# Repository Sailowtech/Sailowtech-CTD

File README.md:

# Sailowtech-CTD - Low-Tech CTD Probe
Welcome on the repository of the Sailowtech CTD Project, an affordable and open-source CTD probe tailored for scientific expeditions.

## Why does this project exist?
After all, Open Source CTD probes already exist? Indeed, there are some great projects like [Open CTD](https://github.com/OceanographyforEveryone/OpenCTD "Open CTD Project") or [CTDizzle](https://github.com/IanTBlack/CTDizzle/tree/main "CTDizzle Project"), but we wanted something more tailored for mid to long term expeditions while allowing a modularity in the embedded sensors. Therefore, we aim to develop a project around a main electronic core and auxiliary cards that can be swapped depending on the research interest. For the moment, we propose a core based on a Raspberry PI Zero 2 W and an auxiliary cards for 2 Atlas Scientific Sensors (Conductivity, Temperature, Dissolved Oxygen, pH...).

## Issues
If you encounter any issues, please use the Issue tracker on GitHub. Please note that this project is still in the development phase and currently undergoing testing.

## Full documentation
The full documentation is accessible under [https://sailowtech.github.io/Sailowtech-CTD/](https://sailowtech.github.io/Sailowtech-CTD/)

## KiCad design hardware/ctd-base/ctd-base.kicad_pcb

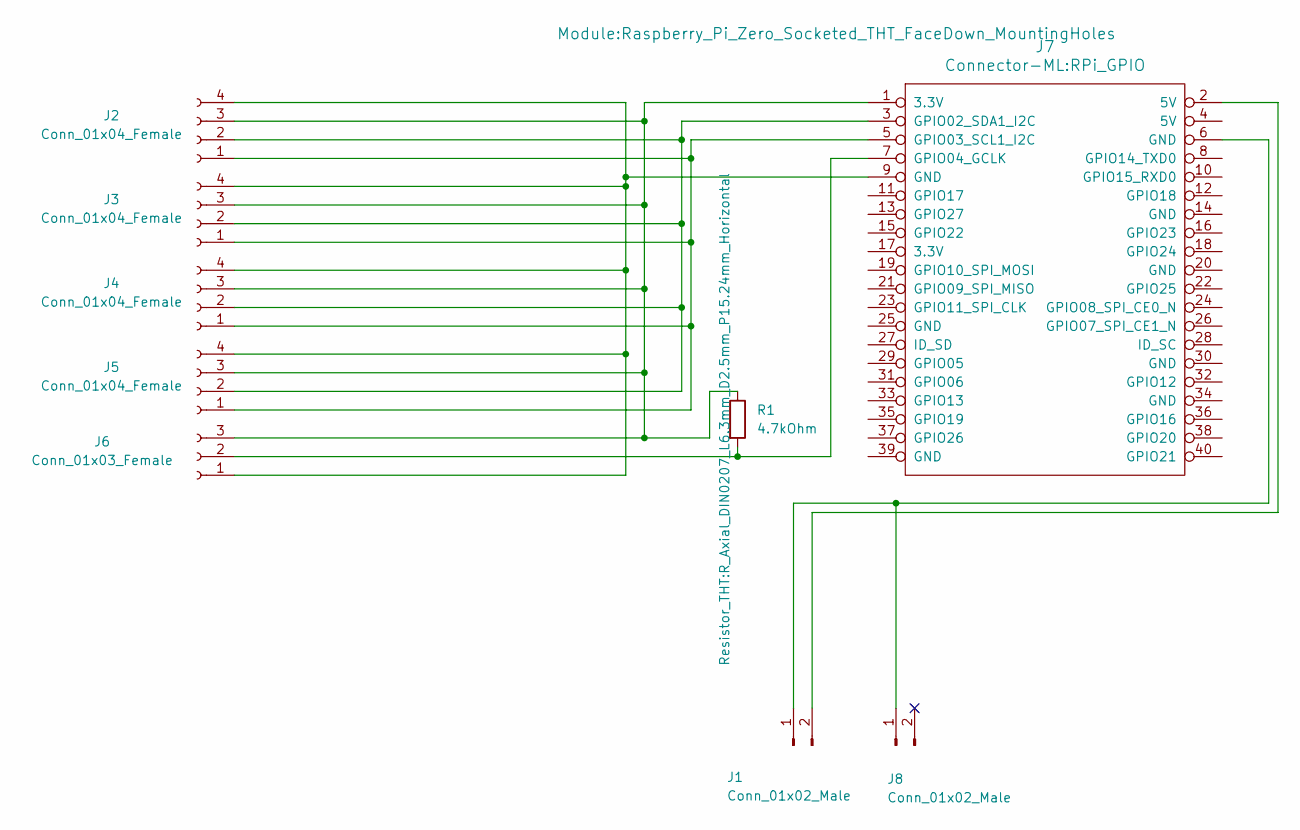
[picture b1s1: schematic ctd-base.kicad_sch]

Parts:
J1, J8: Conn_01x02_Male; JST_XH_S2B-XH-A_1x02_P2.50mm_Horizontal
J2, J3, J4, J5: Conn_01x04_Female; JST_XH_S4B-XH-A-1_1x04_P2.50mm_Horizontal
J6: Conn_01x03_Female; JST_XH_S3B-XH-A_1x03_P2.50mm_Horizontal
J7: Connector-ML:RPi_GPIO; Raspberry_Pi_Zero_Socketed_THT_FaceDown_MountingHoles
R1: 4.7kOhm; R_Axial_DIN0207_L6.3mm_D2.5mm_P15.24mm_Horizontal

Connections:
unnamed: J1.1, J7.6 (GND), J8.1
unnamed: J1.2, J7.2 (5V)
unnamed: J2.1, J3.1, J4.1, J5.1, J7.5 (GPIO03_SCL1_I2C)
unnamed: J2.2, J3.2, J4.2, J5.2, J7.3 (GPIO02_SDA1_I2C)
unnamed: J2.3, J3.3, J4.3, J5.3, J6.3, J7.1 (3.3V), R1.1
unnamed: J2.4, J3.4, J4.4, J5.4, J6.1, J7.9 (GND)
unnamed: J6.2, J7.7 (GPIO04_GCLK), R1.2

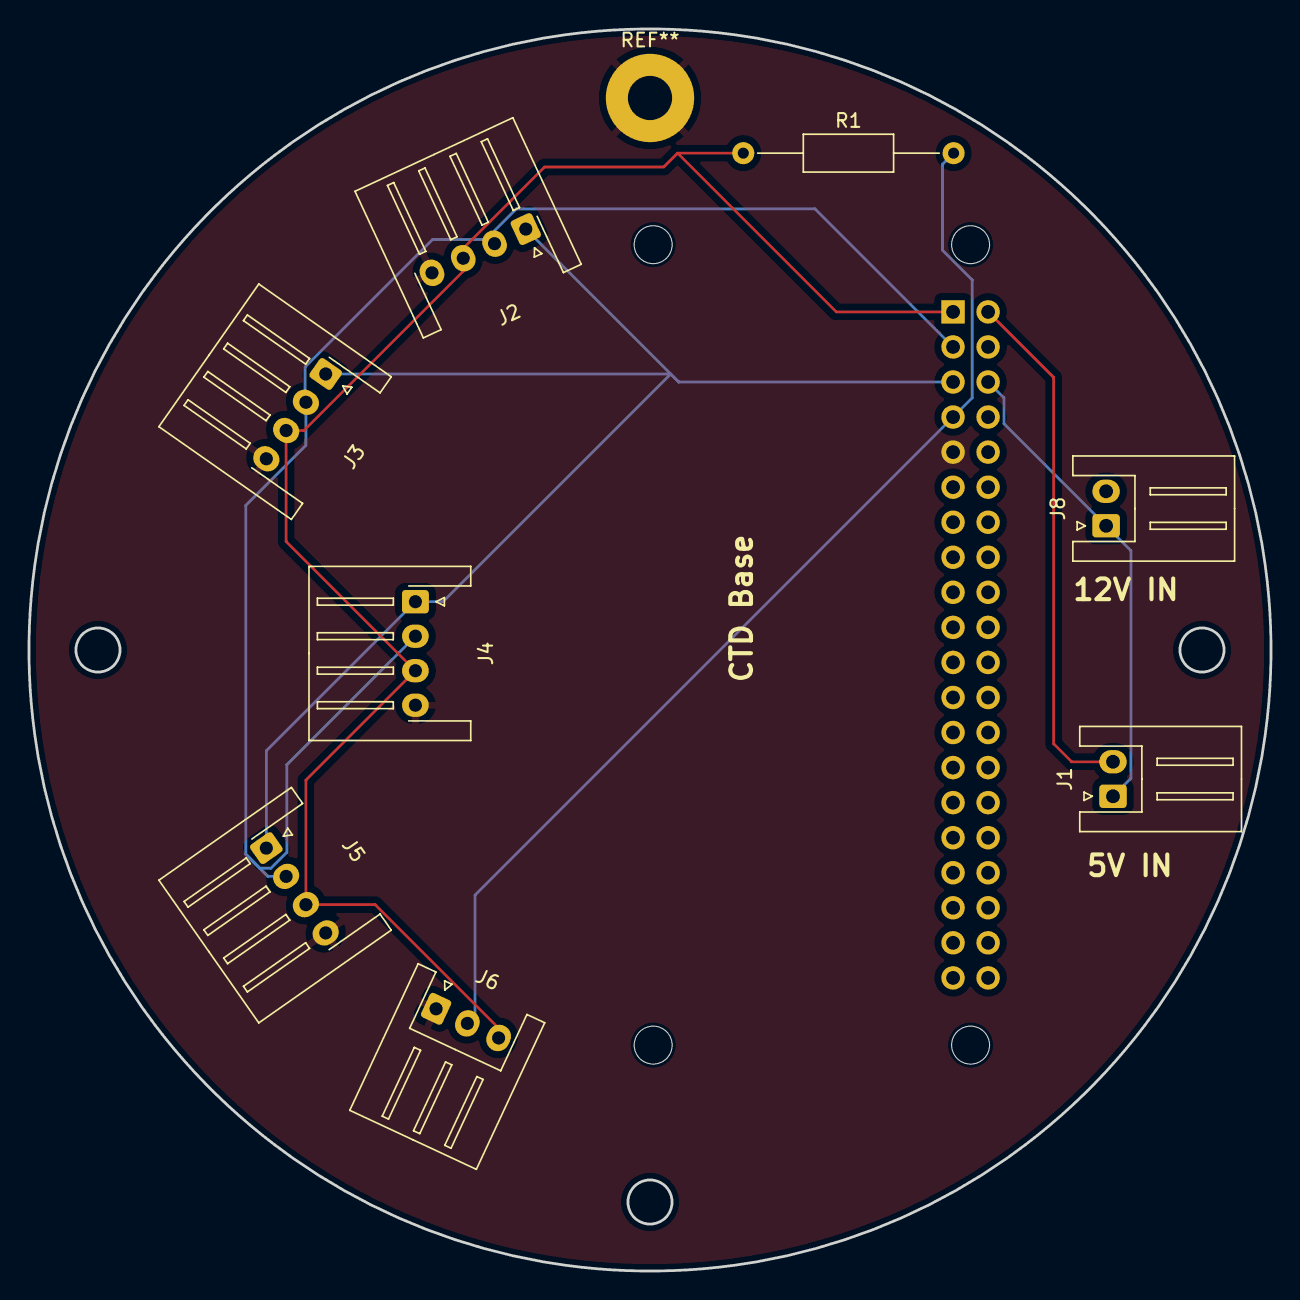
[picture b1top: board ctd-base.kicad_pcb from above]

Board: 2 copper layers, 90.0 x 90.0 mm, 9 parts (1 on the bottom side), 7 nets.

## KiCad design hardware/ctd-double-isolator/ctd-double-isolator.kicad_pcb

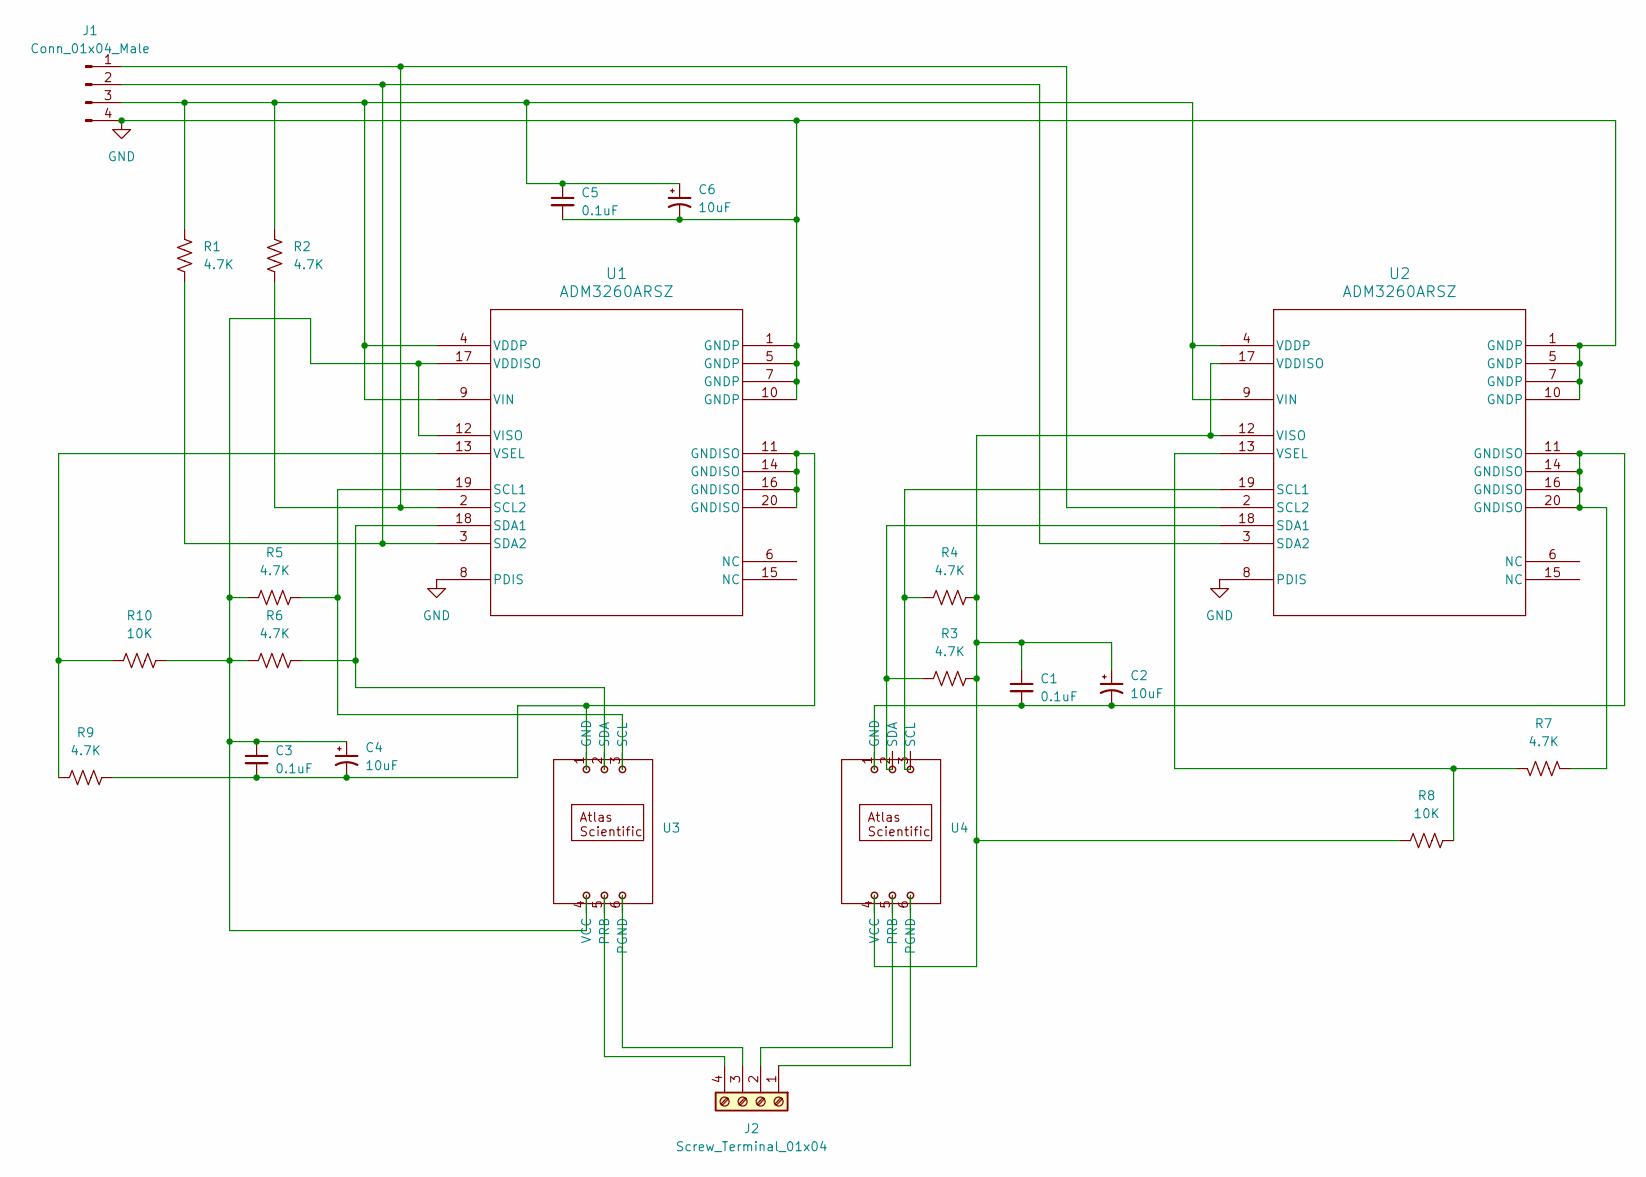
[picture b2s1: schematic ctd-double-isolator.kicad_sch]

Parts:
C1, C3, C5: 0.1uF; C_1812_4532Metric_Pad1.57x3.40mm_HandSolder
C2, C4, C6: 10uF; C_1812_4532Metric_Pad1.57x3.40mm_HandSolder
J1: Conn_01x04_Male; JST_XH_S4B-XH-A-1_1x04_P2.50mm_Horizontal
J2: Screw_Terminal_01x04; TerminalBlock_Phoenix_MPT-0,5-4-2.54_1x04_P2.54mm_Horizontal
R1, R2, R3, R4, R5, R6, R7, R9: 4.7K; R_Axial_DIN0207_L6.3mm_D2.5mm_P10.16mm_Horizontal
R8, R10: 10K; R_Axial_DIN0207_L6.3mm_D2.5mm_P10.16mm_Horizontal
U1, U2: ADM3260ARSZ; RS_20_ADI
U3: Atlas Scientific Dissolved Oxygen
U4: Atlas Scientific RTD Temperature Circuit

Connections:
GND: C5.2, C6.2, J1.4, U1.1 (GNDP), U1.5 (GNDP), U1.7 (GNDP), U1.8 (PDIS), U1.10 (GNDP), U2.1 (GNDP), U2.5 (GNDP), U2.7 (GNDP), U2.8 (PDIS), U2.10 (GNDP)
unnamed: J1.1, R2.2, U1.2 (SCL2), U2.2 (SCL2)
unnamed: J1.2, R1.2, U1.3 (SDA2), U2.3 (SDA2)
unnamed: C5.1, C6.1, J1.3, R1.1, R2.1, U1.4 (VDDP), U1.9 (VIN), U2.4 (VDDP), U2.9 (VIN)
unnamed: J2.1, U4.6 (PGND)
unnamed: J2.2, U4.5 (PRB)
unnamed: J2.3, U3.6 (PGND)
unnamed: J2.4, U3.5 (PRB)
unnamed: R5.2, U1.19 (SCL1), U3.3 (SCL)
unnamed: R6.2, U1.18 (SDA1), U3.2 (SDA)
unnamed: C3.1, C4.1, R5.1, R6.1, R10.2, U1.12 (VISO), U1.17 (VDDISO), U3.4 (VCC)
unnamed: R9.1, R10.1, U1.13 (VSEL)
unnamed: R4.1, U2.19 (SCL1), U4.3 (SCL)
unnamed: R3.1, U2.18 (SDA1), U4.2 (SDA)
unnamed: C1.1, C2.1, R3.2, R4.2, R8.1, U2.12 (VISO), U2.17 (VDDISO), U4.4 (VCC)
unnamed: R7.2, R8.2, U2.13 (VSEL)
unnamed: C3.2, C4.2, R9.2, U1.11 (GNDISO), U1.14 (GNDISO), U1.16 (GNDISO), U1.20 (GNDISO), U3.1 (GND)
unnamed: C1.2, C2.2, R7.1, U2.11 (GNDISO), U2.14 (GNDISO), U2.16 (GNDISO), U2.20 (GNDISO), U4.1 (GND)

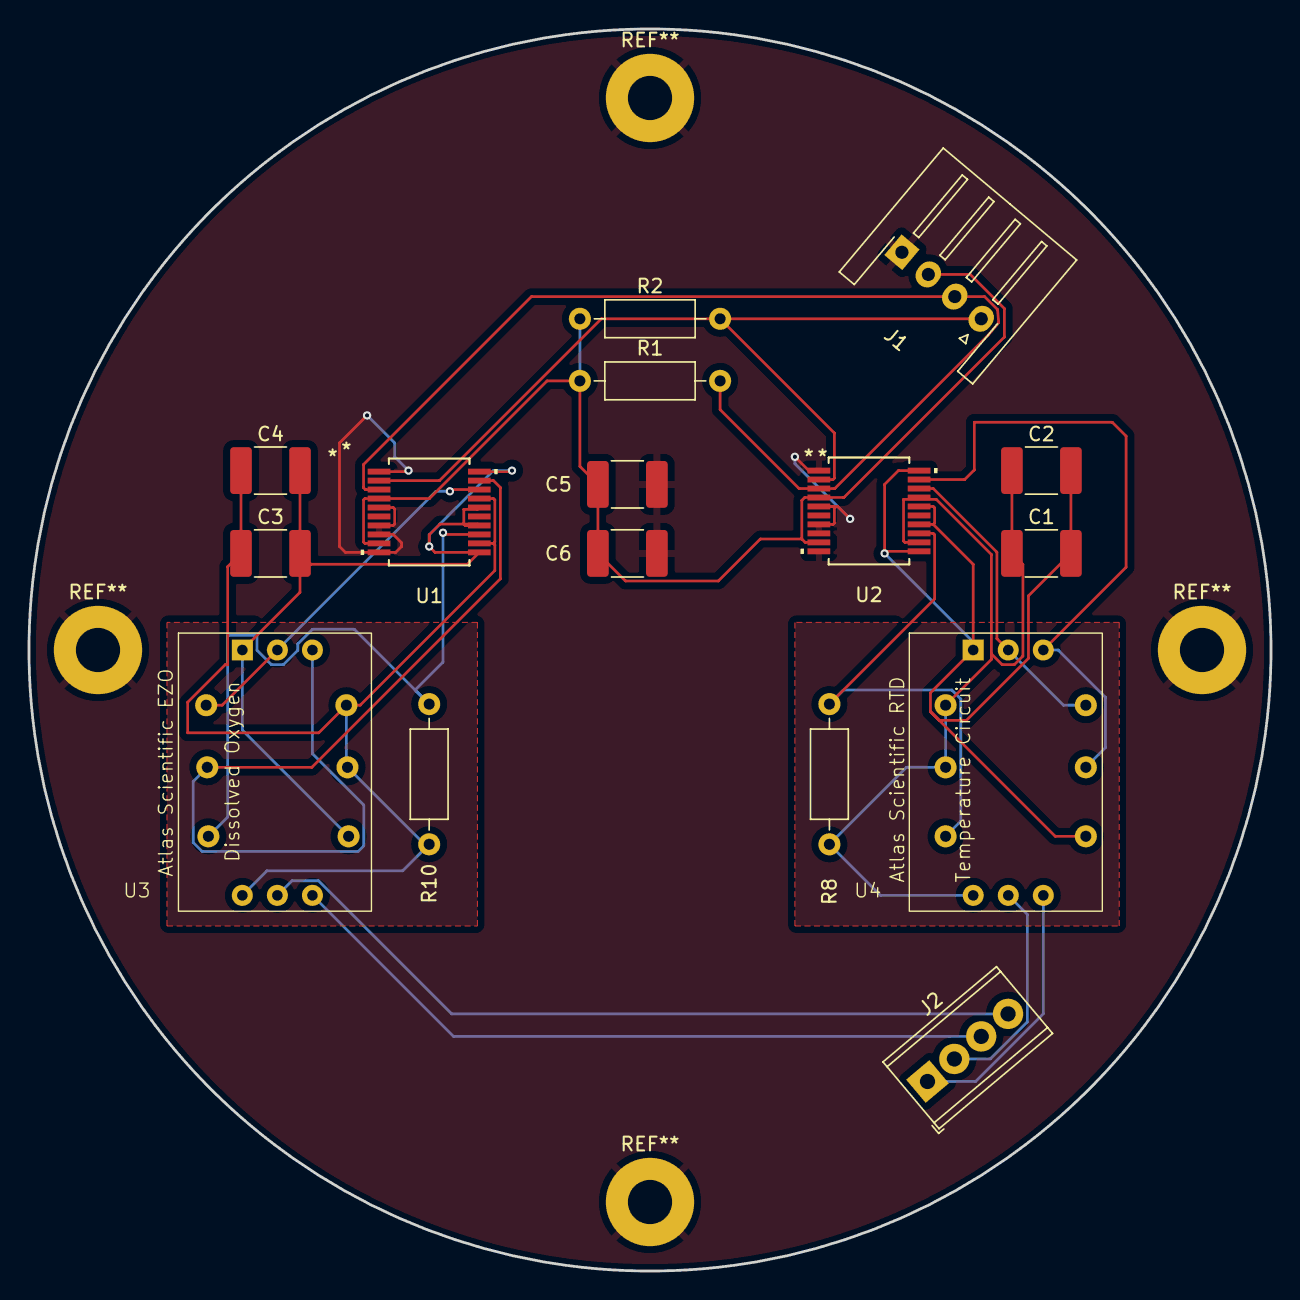
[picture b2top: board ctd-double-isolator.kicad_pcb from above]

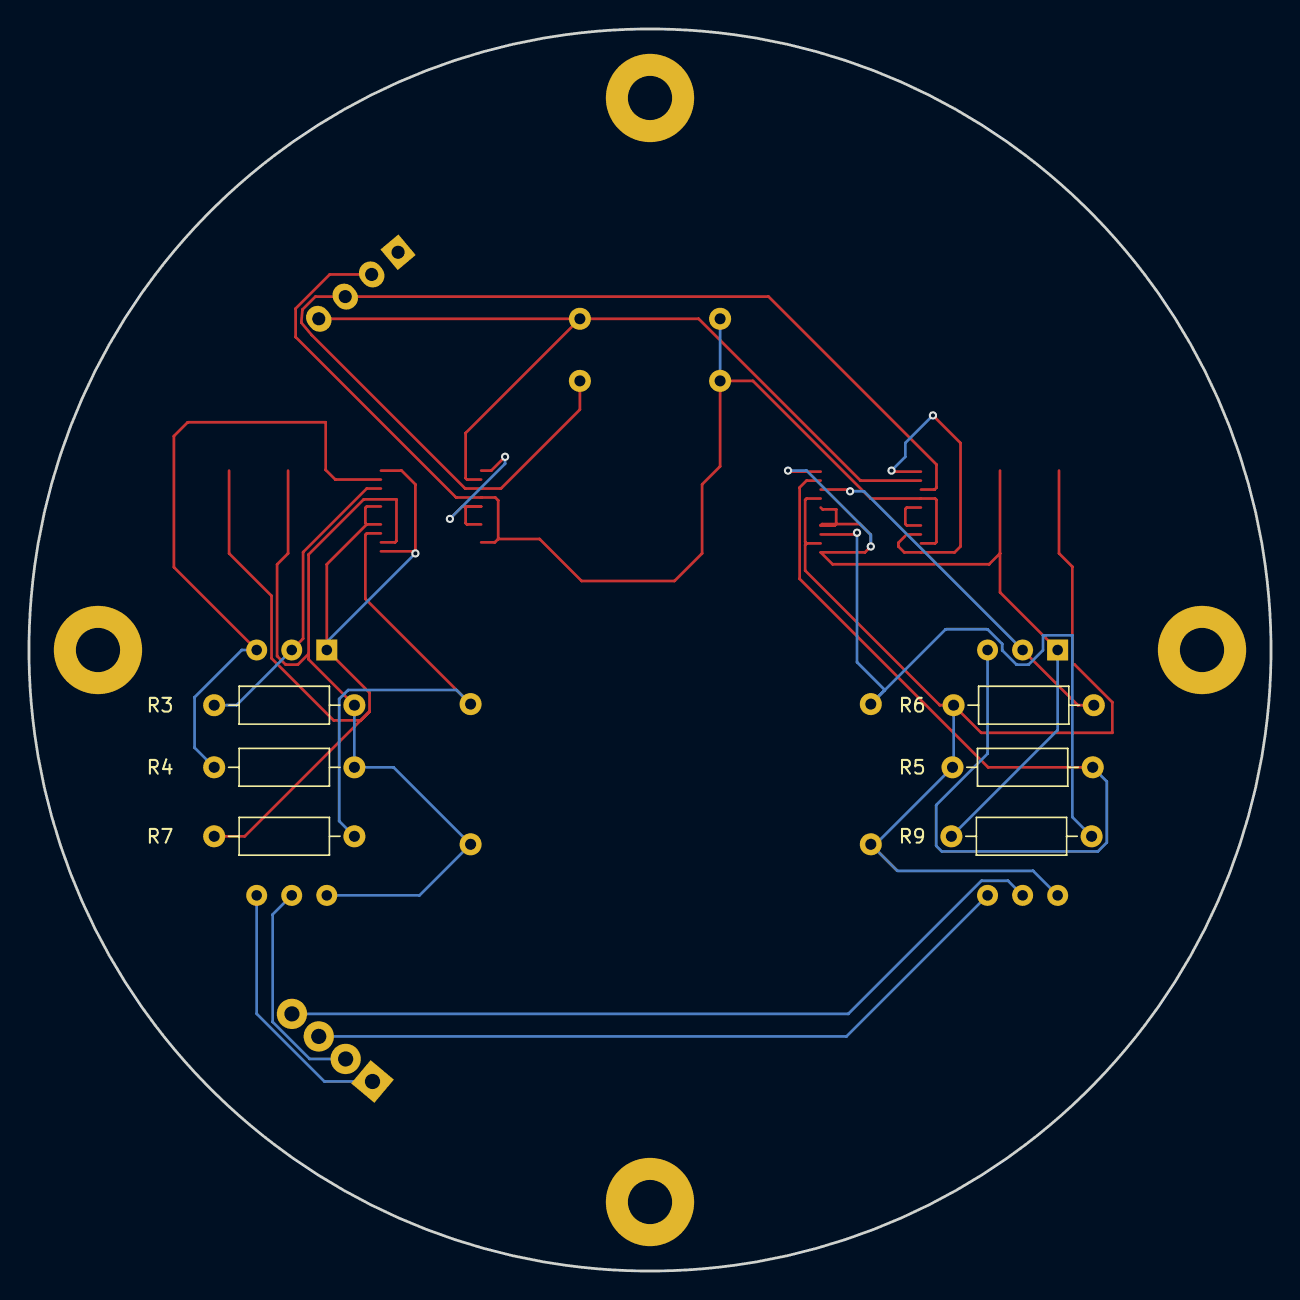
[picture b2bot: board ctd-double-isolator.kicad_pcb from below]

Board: 2 copper layers, 90.0 x 90.0 mm, 22 parts (6 on the bottom side), 18 nets.

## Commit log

2024-07-03 Init
2024-07-03 Initial test with all the sensors except one-wire
2024-07-05 Added SQLite Implementation for measurements and added PCB Designs
2024-07-22 Cleanup workspace to rework soft from scratch
2024-07-22 Use poetry for lib dependencies
2024-07-22 Removed old requirements
2024-07-22 Fix package path + add pyyaml
2024-07-22 Regroup all sensors
2024-07-22 Create base sensors structure
2024-07-22 Add CTD class with base methods
2024-07-22 Removed useless code + started working on new version
2024-07-22 Add str and repr methods
2024-07-22 Add enums for sensors and their brands + hardcode all the sensors
2024-07-22 Use a dataclass hardcode all the sensors, much cleaner
2024-07-22 Move hardcoded values in CTD class + comment code used for yaml config
2024-07-24 Use default sensors + add some properties (getters and setters)
2024-07-24 Add header
2024-07-24 Add smbus lib
2024-08-01 Do some stuff (i dont remember sorry)
2024-08-01 Use generic sensors instead of dataclass
2024-08-01 Add a commands Enum template in generic sensor
2024-08-01 Comment classes as moved in generic
2024-08-01 Reorder args + str() improvements
2024-08-01 Adapt brand subclasses
2024-08-01 Cleanup and use new sublcasses
2024-08-01 Add init template
2024-08-02 Much implementations of Bluerobotics sensor
2024-08-02 Add much .self
2024-08-02 Add common interface to measure value
2024-08-02 Add the bus + some lines to test reading bluerobotics vals
2024-08-02 Repeat measurements
2024-08-02 Try to use mock to simulate fcntl (doesn't exist on windows)
2024-08-02 Did not work out very well
2024-08-02 Push for clone in ctd
2024-08-02 Add requirements
2024-08-02 Add init files and fix paths
2024-08-02 Well that didn't work out
2024-08-02 Test some shit
2024-08-02 Test some shit 2
2024-08-02 Test some shit 3
2024-08-02 Test some shit 4
2024-08-02 Test some shit 5
2024-08-02 Worked w/ example, so try with CTD
2024-08-02 Test some shit 6
2024-08-02 Ugly fix, should work
2024-08-02 remove tests
2024-08-02 De-comment lines
2024-08-02 Cleanup
2024-08-02 Cleanup + finally fix libs imports (use poetry in ctd)
2024-08-03 Remove requirements as we use poetry in the ctd
2024-08-03 Return multiple values when asked to measure
2024-08-03 Print all values collected by the pressure sensor
2024-08-03 Add protocol pdf
2024-08-03 Add calibrate method template
2024-08-03 Remove useless
2024-08-04 Add keyboard lib
2024-08-04 Add enum for value fields
2024-08-04 Refactor output fields enum name
2024-08-04 Save all datas and export them at the end + add a key to stop the program
2024-08-05 Stop using keyboard lib as need to be root on linux to execute it
2024-08-05 Use a user-defined pressure threshold to determine the end of the measurements (ctd goes up)
2024-08-05 Create unique date-based data files to prevent overwriting them with next measurement
2024-08-05 Add log message when stopping because going up
2024-08-05 Remove useless code and comment temporary unused code
2024-08-05 Add command
2024-08-08 Better poetry explanation
2024-08-08 First test of using both Atlas and BlueRobotics sensors
2024-08-08 Forgot to add sensors
2024-08-09 Move Depth Sensor up in the list
2024-08-09 Ask for value before reading it
2024-09-03 Small changes in documentation
2024-10-04 Move schematics in proper folder
2024-12-30 Added mkDocs structure
2024-12-31 Create mkdocs.yml for mkDocs Workflow
2025-01-02 Changed project structure and added API dependencies
2025-01-02 Refactoring of types
    The types have been changed to allow for more modularity. This prepares the current structure for different output types (database) and more sensor devices
2025-01-03 Adapted Documentation
    Documentation should build correctly with material theme and inline documentation of CTD class
2025-01-03 Deployed ae4651c with MkDocs version: 1.6.1
2025-01-04 Type refactorings
    Further type refactorings and adaptations
2025-01-04 First draft for image building action
2025-01-04 Attempt build of basic Raspbian image
2025-01-04 Run build as root
2025-01-04 Change build to upload artifact and install the ctd software
2025-01-04 Adapt stage paths
2025-01-04 Fixed git clone command, changed job name, and moved installation script to chroot script
2025-01-04 Added ensurepath for pipx to work
2025-01-04 Changed documentation structure
    Split documentation into Hardware / Operating System / Software
2025-01-04 Removed space from command in stage
2025-01-05 Setup basic network
2025-01-05 Fix install path and skip creation of stage2 image file
2025-01-05 Fixed pipe symbol in network setup
2025-01-05 Append to wpa_supplicant file instead of overwriting in case there is already content
2025-01-05 Ensure ctd user stays active and change installation of poetry
2025-01-05 Change network management from wpa_supplicant to NetworkManager
2025-01-05 Test Github Action with Release
2025-01-05 Changed network again to run with iwd
2025-01-05 Add additional config for iwd
2025-01-05 Create iwd directory
2025-01-06 Change action so that it runs on tagged versions
2025-01-06 Add required permissions for Release Action
2025-01-06 Enable I2C support to image
2025-01-06 Change name of the image built
2025-01-06 Add further documentation
2025-01-06 Fixed README.md whoopsie
2025-01-06 Add newline to build config
2025-01-07 Added Config Parser and Logger
2025-01-07 Deployed 539a0d5 with MkDocs version: 1.6.1
2025-02-05 Add Hotspot instead of connecting to mobile device
2025-02-05 chown git directory to avoid errors with permissions
2025-02-05 Added debug statements
2025-02-06 Moved network config from iwd to hostapd
2025-02-06 Add missing package dhcpcd
2025-02-06 Fix poetry install and path in image build
2025-02-06 Upgraded to poetry 2.0
2025-02-06 Changed path management and fixed some smaller bugs
2025-02-08 Created mock elements for easier testing and added saving of measurements to database
2025-02-09 Added basic web api with csv export
2025-02-10 Run startable in web api. Installation of pyenv with correct python version
2025-02-10 Removed pyenv from install list and added official installer for it into build
2025-02-10 Fixed pyenv location in build
2025-02-10 Added some documentation
2025-02-11 Added required packages for pyenv
2025-02-11 Use absolute path of python env
2025-02-11 Install pyenv and python version as ctd user
2025-02-11 Correctly setup poetry as ctd user
2025-02-12 Return float value of depth as a measured value for the Bluerobotics depth sensor
2025-02-12 Working version with atlas_i2c library
2025-02-12 Add second sensor loop in order to minimize delay
2025-02-12 Add start entry for webapp
2025-02-12 Fixed sleep and added usage documentation
2025-02-13 Remove automatic reloading of uvicorn app
2025-02-13 Change installation documentation
2025-02-13 Change webapp port
2025-02-13 Create autostart file
2025-02-13 Changed structure of the software. Added main thread loop. Added different run categories.
2025-02-13 Adapted docs to latest changes
2025-02-13 Release to first working minor version 0.1.0
2025-02-13 Add frontend structure and api static serving
2025-02-13 Fixed typo in service file
2025-02-13 Add frontend build to image build process
2025-02-13 Adapted logger color reset
2025-02-13 Adapt version to 0.1.1
2025-02-13 Very basic web interface with vue. Still buggy, but generally usable
2025-02-13 Change web endpoint for prod
2025-02-14 Fix systemd service file creation
2025-02-14 Fix bug where `this` was undefined in production build
2025-02-14 Fix config parsing file location finding
2025-02-14 Fix relative location of web build
2025-02-14 Add more verbose logging
2025-02-14 Changed AP setup to nmcli to fix weird bug that caused AP to not be available after reboot
2025-02-14 Updated documentation
2025-02-14 No loooosy looooosy
2025-02-15 Switched database ORM to peewee
2025-02-15 Remove python version restriction of PonyORM and remove pyenv build
2025-02-15 Added support for basic measurement visualization and metrics
2025-02-16 Added basic time sync
2025-02-16 Fix ntp disabling error
2025-02-16 Enable NetworkManager in build
2025-02-16 Fixed loading of path for database file
2025-02-16 Fixed division by 1000 to integer in frontend time syncing
2025-02-16 Added correct Post Data parsing with request model
2025-02-16 Changed listening interfaces for web-debug
2025-02-16 Fixed NetworkManager startup on boot
2025-02-16 Deployed 6e6cf58 with MkDocs version: 1.6.1
2025-03-17 Fix order of CSV Export columns. Fixes #11
2025-03-17 Deployed 8af075f with MkDocs version: 1.6.1
2025-09-09 Deployed 60746a6 with MkDocs version: 1.6.1
2025-11-01 Added i2c-tools to installed packages to simplify sensor debugging
2025-11-01 Deployed ab38001 with MkDocs version: 1.6.1
